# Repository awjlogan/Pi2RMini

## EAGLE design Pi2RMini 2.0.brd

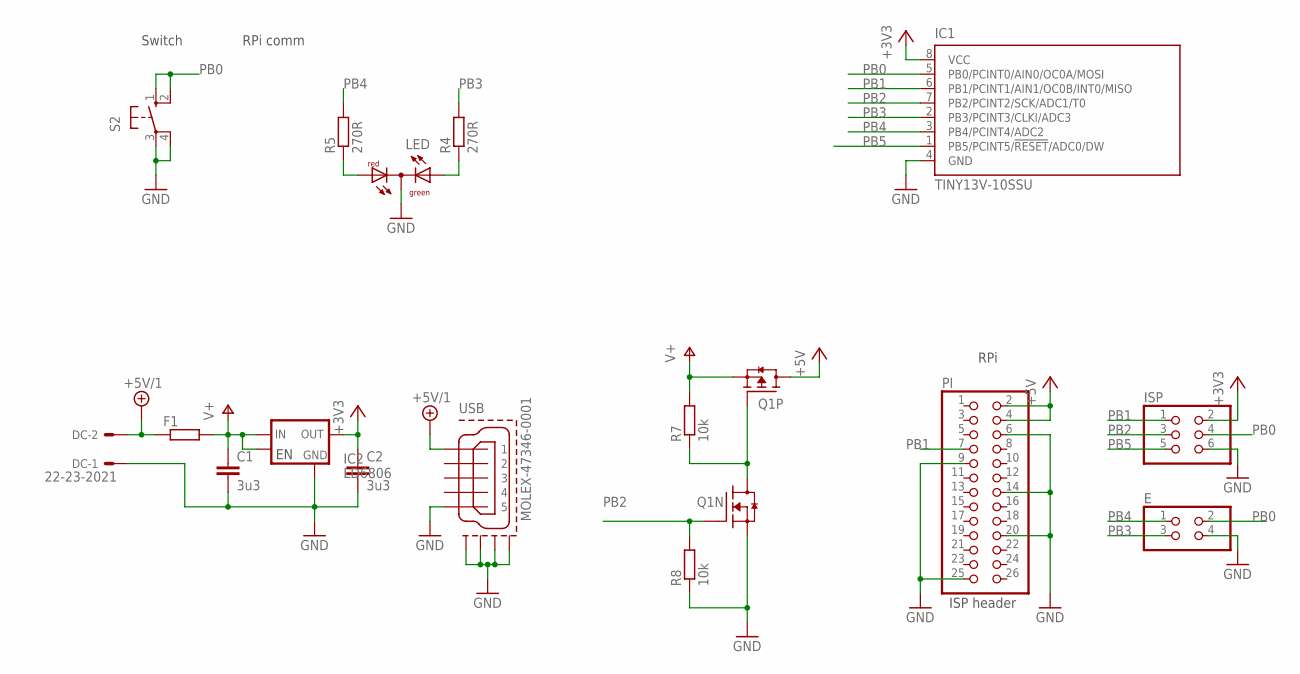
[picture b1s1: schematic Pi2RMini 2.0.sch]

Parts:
C1, C2: 3u3; C0603
DC: 22-23-2021
E: PINHD-2X2; 2X02
F1: R-EU_R1210; R1210
IC1: TINY13V-10SSU; 8S1
IC2: LD6806; SOT-753
ISP: PINHD-2X3; 2X03
LED: DUOLED-CC; SOT-23
PI: PINHD-2X13; 2X13
Q1: BSL215; 6TSOP
R4, R5: 270R; R0603
R7, R8: 10k; R0603
S2: 10-XX; B3F-10XX
USB: MOLEX-47346-0001; MOLEX-47364-0001

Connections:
+3V3: C2.1, IC1.8 (VCC), IC2.5 (OUT), ISP.2
+5V: PI.2, PI.4, Q1.4 (D)
+5V/1: DC.2, F1.1, USB.1
GND: C1.2, C2.2, DC.1, E.4, IC1.4 (GND), IC2.2 (GND), ISP.6, LED.3 (C), PI.6, PI.9, PI.14, PI.20, PI.25, Q1.5 (S), R8.1, S2.3, S2.4 (P1), USB.5, USB.GND1, USB.GND2, USB.GND3, USB.GND4
unnamed: Q1.3 (G), Q1.6 (D), R7.1
PB0: E.2, IC1.5 (PB0/PCINT0/AIN0/OC0A/MOSI), ISP.4, S2.1 (S), S2.2 (S1)
PB1: IC1.6 (PB1/PCINT1/AIN1/OC0B/INT0/MISO), ISP.1, PI.7
PB2: IC1.7 (PB2/PCINT2/SCK/ADC1/T0), ISP.3, Q1.1 (G), R8.2
PB3: E.3, IC1.2 (PB3/PCINT3/CLKI/ADC3), R4.2
PB3': LED.2 (AG), R4.1
PB4: E.1, IC1.3 (PB4/PCINT4/ADC2), R5.2
PB4': LED.1 (AR), R5.1
PB5: IC1.1 (PB5/PCINT5/!RESET!/ADC0/DW), ISP.5
V+: C1.1, F1.2, IC2.1 (IN), IC2.3 (EN), Q1.2 (S), R7.2

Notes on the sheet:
Switch
RPi comm
ISP header
RPi

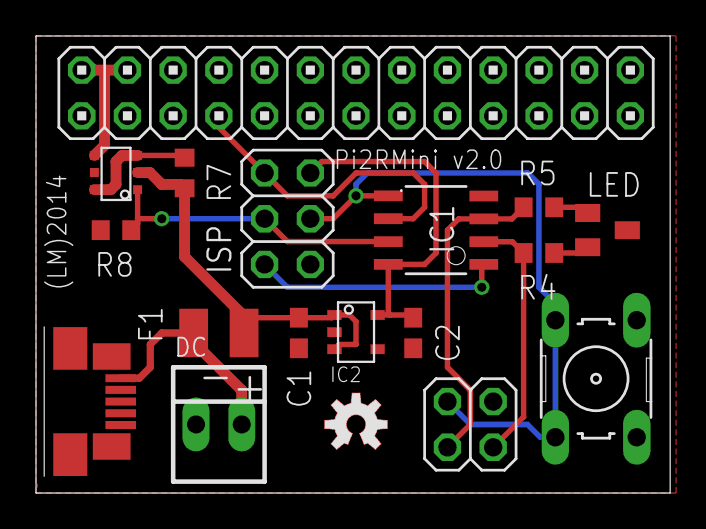
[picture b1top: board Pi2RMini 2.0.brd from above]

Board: 2 copper layers, 35.2 x 25.4 mm, 17 parts (0 on the bottom side), 14 nets.

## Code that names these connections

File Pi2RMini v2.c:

/*
 * Pi2RMini.c
 *
 * Pi2R Mini device firmware for v2.x boards
 * Logan Microelectronics 2013-2014
 * http://awjlogan.wordpress.com
 * https://github.com/awjlogan/pi2rmini
 *
 * Written in AVR Studio 5 for AVR GCC
 * Target: Atmel ATTiny13
 * 4.8 MHz internal oscillator / 8 = 600 kHz
 * Pins:	1	!RST					PB5
 *			2	Green LED				PB3
 *			3	Red LED					PB4
 *			4	GND		
 *			5	Switch					PB0
 *			6	RPi communication line	PB1
 *			7	RPi MOSET				PB2
 *			8	+3V3
 *
 * Fuse calculated:		FF 69 (http://www.engbedded.com/fusecalc)
 * avrdude arguments:	-U lfuse:w:0x69:m -U hfuse:w:0xff:m
 * for: 4.8 MHz int osc, 14CK + 64 ms startup, CKDIV, no WDT, SPI enabled, !RST enabled, no BOD
 *
 * To change the startup, reset, and shutdown delays, alter lines with 'seconds = xx'. The TMR0 interrupt hits every
 * ~100 ms, so the seconds value should be 'delay in seconds x 10'. The variable 'flash' acts in the same way.
*/			

#define F_CPU		600000UL

#include <avr/io.h>
#include <avr/interrupt.h>
#include <util/delay.h>

// Status register definitions
#define	PI_ERROR	1
#define PI_ON		8
#define PI_OFF		16
#define BUTTON		32

#define PI_COMM		PINB1

// Pin assignments
#define SW			0x01
#define PI_FET		0x04
#define LED_G		0x08
#define LED_R		0x10

// common cathode status LED on/off
#define RED_OFF		PORTB &= ~(LED_R)
#define RED_ON		PORTB |= LED_R
#define GRN_OFF		PORTB &= ~(LED_G)
#define GRN_ON		PORTB |= LED_G

// Function prototypes
static void setup(void);
static void button(void);
static void reset(void);

// Global variables
static volatile uint8_t state = 0;
static volatile uint8_t flash = 0;
static volatile uint16_t seconds = 0;

int main(void)
{
	setup();
	state |= PI_OFF;
	RED_ON;
	GRN_OFF;
	
	// check status registers and respond
	while(1)
    {	
		if (state & BUTTON) {
			// disable PCINT while button press is handled
			PCMSK &= ~(1<<PCINT0);
			state &= ~(BUTTON);
			_delay_ms(50);					// debounce
			if (!(PINB & PINB0)) {
				button();
			}
			PCMSK |= (1<<PCINT0);
		}
		
		// flash red LED if in error state
		if (state & PI_ERROR) {
			if (!flash) {
				PORTB ^= LED_R;
				flash = 2;
			}
		}
	}	
}

static void button(void) {
	if (state & PI_OFF) {
		state = PI_ON;
		PORTB |= PI_FET;
		GRN_ON;
		RED_ON;
		
		// wait 60 secs for RPi to start up
		seconds = 600;
		while(PINB & (1<<PI_COMM)) {
			if (!seconds) {
				state |= PI_ERROR;
				GRN_OFF;
				return;
			}
		}
		RED_OFF;
		return;
	}
	
	if (state & PI_ON) {
		// check for forced reset - 4 s press
		seconds = 40;
		RED_ON;
		GRN_OFF;
		while (!(PINB & (1<<PINB0))) {
			// flash red/green
			if (!flash) {
				PORTB ^= (LED_G + LED_R);
				flash = 2;
			}
			// time up, reset!
			if (!seconds) {
				cli();
				reset();
				while(!(PINB & (1<<PINB0)));
				sei();
				return;
			}
		}
		
		// don't turn off in error state
		if (state & PI_ERROR) {
			RED_ON;
			GRN_OFF;
			return;
		}		
		
		// send shutdown signal, wait 10 secs for response
		RED_ON;
		GRN_OFF;
		DDRB |= (1<<DDB1);
		PORTB |= (1<<PINB1);
		_delay_ms(1);
		PORTB &= ~(1<<PINB1);
		_delay_ms(100);
		DDRB &= ~(1<<DDB1);
		PORTB |= (1<<PINB1);
		seconds = 100;
		while(PINB & (1<<PI_COMM)) {
			if (!seconds) {
				RED_ON;
				GRN_OFF;
				state |= PI_ERROR;
				return;
			}
		}
		
		// wait 30 secs, then shutdown
		GRN_ON;
		seconds = 300;
		while(seconds) {}
		reset();
		return;
	}
}

static void reset(void) {
	state = PI_OFF;
	PORTB = LED_R;
	DDRB = ((1<<DDB2)|(1<<DDB3)|(1<<DDB4));	
	return;
}

static void setup(void) {
	cli();
	
	// oscillator setup
	CLKPR = 0x80;	
	CLKPR = 0x01;
	
	// interrupt setup
	PCMSK |= 1 << PCINT0;	
	GIMSK |= 1 << PCIE;
	TIMSK0 |= 1 << TOIE0;
	
	// TMR0 setup
	// TCNT0 = 21 will give 0.1s count up time
	TCCR0A = 0;		
	TCCR0B = 0x05;	
					
	// PORTB setup
	// MCUCR |= (1<<PUD); // for v2.x, pull ups are enabled
	DDRB = ((1<<DDB2)|(1<<DDB3)|(1<<DDB4));
	PORTB |= ((1<<PINB0)|(1<<PI_COMM));	

	sei();
}

ISR(PCINT0_vect) {
	state |= BUTTON;
}

ISR(TIM0_OVF_vect) {
	if(flash) flash--;
	if(seconds) seconds--;
	TCNT0 = 21;					// reset for ~100 ms interval
}
